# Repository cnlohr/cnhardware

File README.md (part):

# hardware

My random junk repo for random things.

If you're looking for 

**NOTE** FOR PULL REQUESTS: I DO NOT ACCEPT MASS ADDS.  If you have 5-6 really awesome parts, I'll accept a pull request, but if you have say 10+ parts, I will not.  Select only the neatest.  Also, make sure JLCPCB offers the parts, if they're intended for board mounting!

## Shortcuts

* [Discussion of ferrite cores and what their recommended power is](https://www.mag-inc.com/Media/Magnetics/File-Library/Product%20Literature/Ferrite%20Literature/Ferrite-Transformer-Design-2021.pdf)
* [Another doc like the above, but with different info](https://www.mag-inc.com/getattachment/Products/Ferrite-Cores/MagneticsFerritePowerDesign2013.pdf?)
* [Discussion of building ferrite cores](https://www.st.com/resource/en/newsletter/Wurth_Design_Considerations_Munich.pdf)
* [Breakdown voltages of enameld copper wire](https://www.edaboard.com/threads/breakdown-voltage-of-enamelled-copper-wire.407275/)
* [Enameld wire datasheet](https://www.elektrisola.com/en-us/Products/Enamelled-Wire/Technical-Data)

## Small Combo Fets

|Datasheet|LCSC|Footprint|Description|Cost 150|
|--|--|--|--|--|
|[PB544JU](https://datasheet.lcsc.com/lcsc/2005181005_NIKO-Semicon-PB544JU_C532969.pdf)|[C532969](https://www.lcsc.com/product-detail/MOSFETs_NIKO-Semicon-PB544JU_C532969.html)|DFN-6-EP(3x2)|Dual N 20v, 8m, 1.2v, 1584pF|0.1376|
|[SE4625](https://datasheet.lcsc.com/lcsc/2008291435_SINO-IC-SE4625_C730094.pdf)|[C730094](https://www.lcsc.com/product-detail/MOSFETs_SINO-IC-SE4625_C730094.html)|DFN-6L-EP(2x2)|P and N, 12v, 28/57m, 1.2v, 469pF|0.0508|
|[SED5852](https://datasheet.lcsc.com/lcsc/2208251800_SINO-IC-SED5852_C238715.pdf)|[C238715](https://www.lcsc.com/product-detail/MOSFETs_SINO-IC-SED5852_C238715.html)|DFN-6-EP(2x2)|P+Schottky, 20v, 90m, 1.2v, 540pF|0.0250|
|[WPM2006](https://datasheet.lcsc.com/lcsc/1808311525_WILLSEMI-Will-Semicon-WPM2006-6-TR_C167136.pdf)|[C167136](https://www.lcsc.com/product-detail/MOSFETs_WILLSEMI-Will-Semicon-WPM2006-6-TR_C167136.html)|DFN-6L-EP(2x2)|P+Schottky, 20v, 90m, 1.2v, 480pF|0.0579|
|[YJQ2301A](https://datasheet.lcsc.com/lcsc/2206101730_Yangzhou-Yangjie-Elec-Tech-YJQ2301A_C2942370.pdf)|[C2942370](https://www.lcsc.com/product-detail/MOSFETs_Yangzhou-Yangjie-Elec-Tech-YJQ2301A_C2942370.html)|DFN-6-EP(2x2)|Dual P 20v, 60m, 1.2v, 438pF|0.0872**|
|[HSCB20D03](https://datasheet.lcsc.com/lcsc/2105241828_HUASHUO-HSCB20D03_C2828494.pdf)|[C2828494](https://www.lcsc.com/product-detail/MOSFETs_HUASHUO-HSCB20D03_C2828494.html)|DFN-6-EP(2x2)|Dual P 20v, 90m, 1.5v, 331pF|0.0927|
|[HSCB2903](https://datasheet.lcsc.com/lcsc/2110221630_HUASHUO-HSCB2903_C2903561.pdf)|[C2903561](https://www.lcsc.com/product-detail/MOSFETs_HUASHUO-HSCB2903_C2903561.html)|DFN-6L-EP(2x2)|P and N, 20v, 40m, 100m, 1.5v, 310pF|0.1273||
|[NCE30D0808J](https://datasheet.lcsc.com/lcsc/2103121415_Wuxi-NCE-Power-Semiconductor-NCE30D0808J_C2686534.pdf)|[C2686534](https://www.lcsc.com/product-detail/MOSFETs_Wuxi-NCE-Power-Semiconductor-NCE30D0808J_C2686534.html)|DFN-6-EP(2x2)|Dual N, 30v, 35m, 2.5v, 558pF|0.1729|
|[SIA517DJ-T1-GE3](https://datasheet.lcsc.com/lcsc/2108150330_JSMSEMI-SIA517DJ-T1-GE3_C2874705.pdf)|[C2874705](https://www.lcsc.com/product-detail/MOSFETs_JSMSEMI-SIA517DJ-T1-GE3_C2874705.html)|WDFN-6-EP(2x2)|P and N, 12v, 30/70m, 590pF|0.1764|
|[DMP1046UFDB-7](https://datasheet.lcsc.com/lcsc/1912111437_Diodes-Incorporated-DMP1046UFDB-7_C461048.pdf)|[C461048](https://www.lcsc.com/product-detail/MOSFETs_Diodes-Incorporated-DMP1046UFDB-7_C461048.html)|U-DFN2020-6D|Dual N, 12v, 60m, 1.3v, 915pF|0.20|

## Interesting Fets

|Datasheet|LCSC|Footprint|Description|Cost 150|
|--|--|--|--|--|
|[WNM2096-3/TR](https://datasheet.lcsc.com/lcsc/2201121500_WILLSEMI-Will-Semicon-WNM2096-3-TR_C2931326.pdf)**|[C2931326](https://www.lcsc.com/product-detail/MOSFETs_WILLSEMI-Will-Semicon-WNM2096-3-TR_C2931326.html)|DFN-3(1x0.6)|N, 20v, 400m, 1.7v, 20pF (On Order)|0.0626|
|[TPDMN26D0UFB4](https://datasheet.lcsc.com/lcsc/2108132030_TECH-PUBLIC-TPDMN26D0UFB4_C970037.pdf)|[C970037](https://www.lcsc.com/product-detail/MOSFETs_TECH-PUBLIC-TPDMN26D0UFB4_C970037.html)|DFN-3(1x0.6)|N, 20v, 500m, 1.2v, 120pF (Cheap, Basic Sevice, Tiny, Not great but good for signals)|.0242|
|[DMN3110LCP3-7](https://datasheet.lcsc.com/lcsc/1912111437_Diodes-Incorporated-DMN3110LCP3-7_C443826.pdf)|[C443826](https://www.lcsc.com/product-detail/MOSFETs_Diodes-Incorporated-DMN3110LCP3-7_C443826.html)|X2-DSN1006-3|N, 30v, 80m, 1.3v, 140pF Wicked Awesome Case|0.1775|
|[TPM2008EP3](https://datasheet.lcsc.com/lcsc/2108132030_TECH-PUBLIC-TPM2008EP3_C2682293.pdf)|[C2682293](https://www.lcsc.com/product-detail/MOSFETs_TECH-PUBLIC-TPM2008EP3_C2682293.html)|DFN1006-3L(1x0.6)|N, 20v, 130m, 1.2v, 120pF|0.0278|
|[PNM3FD20V1E](https://datasheet.lcsc.com/lcsc/2108150430_Shanghai-Prisemi-Elec-PNM3FD20V1E_C2875806.pdf)|[C2875806](https://www.lcsc.com/product-detail/MOSFETs_Shanghai-Prisemi-Elec-PNM3FD20V1E_C2875806.html)|DFN-3L(1x0.6)|N, 20v, 200m, 1.1v, 48pF|0.0256|
|[DMN2990UFA-7B](https://datasheet.lcsc.com/lcsc/1804250226_Diodes-Incorporated-DMN2990UFA-7B_C151598.pdf)|[C151598](https://www.lcsc.com/product-detail/MOSFETs_Diodes-Incorporated-DMN2990UFA-7B_C151598.html)|XFDFN-3(0.6x0.8)|N, 20v, 900m, 1.3v, 30pF|0.0544|
|[HSCB2307](https://datasheet.lcsc.com/lcsc/2010160905_HUASHUO-HSCB2307_C845602.pdf)|[C845602](https://www.lcsc.com/product-detail/MOSFETs_HUASHUO-HSCB2307_C845602.html)|DFN-6L(2x2)|P, 20v, 15m, 1v, 2100pF|0.0789|
|[G66](https://datasheet.lcsc.com/lcsc/1809251724_GOFORD-G66_C239037.pdf)|[C239037](https://www.lcsc.com/product-detail/MOSFETs_GOFORD-G66_C239037.html)|DFN-6L(2x2)|P, 16v, 45m, 1.25v, 740pF|0.0499|
|[DMP1009UFDF](https://datasheet.lcsc.com/lcsc/2003091237_Diodes-Incorporated-DMP1009UFDF-7_C493499.pdf)|[C493499](https://www.lcsc.com/product-detail/MOSFETs_Diodes-Incorporated-DMP1009UFDF-7_C493499.html)|U-DFN2020-6|P, 12v, 11m, 1.1v, 1860pF|0.4530|
|[PJM01N20KDC](https://datasheet.lcsc.com/lcsc/2203092030_PJSEMI-PJM01N20KDC_C2981470.pdf)|[C2981470](https://www.lcsc.com/product-detail/MOSFETs_PJSEMI-PJM01N20KDC_C2981470.html)|DFN-3L(1x0.6)|N, 20v, 180m, 1.3v, 56pF|0.0259|
|[AP4580](https://datasheet.lcsc.com/lcsc/2108150030_ALLPOWER-ShenZhen-Quan-Li-Semiconductor-AP4580_C2849569.pdf)|[C2849569](https://www.lcsc.com/product-detail/MOSFETs_ALLPOWER-ShenZhen-Quan-Li-Semiconductor-AP4580_C2849569.html)|SOT-23-8L|2N and 2P Full Bridge|0.0635|
|[DMC3730UFL3-7](https://datasheet.lcsc.com/lcsc/1912111437_Diodes-Incorporated-DMC3730UFL3-7_C460973.pdf)|[C460973](https://www.lcsc.com/product-detail/MOSFETs_Diodes-Incorporated-DMC3730UFL3-7_C460973.html)|X2-DFN1310-6|Complementary P- and N- 1A, 30V TTL level FETs|0.0539|

## Special FETs

|Datasheet|LCSC|Footprint|Description|Cost 150|
|--|--|--|--|--|
|[DMZ6005E](https://datasheet.lcsc.com/lcsc/2206061716_ARK-micro-DMZ6005E_C3031422.pdf)|[C3031422](https://www.lcsc.com/product-detail/MOSFETs_ARK-micro-DMZ6005E_C3031422.html)|SOT-23|Depletion Mode N-Fet (Normally on)|0.0626|

## Interesting BJTs

|Datasheet|LCSC|Footprint|Description|Cost 150|
|--|--|--|--|--|
|[2SC4226](https://datasheet.lcsc.com/lcsc/2009141834_Slkor-SLKORMICRO-Elec--2SC4226-R25_C781319.pdf)|[C781319](https://www.lcsc.com/product-detail/Bipolar-Transistors-BJT_Slkor-SLKORMICRO-Elec-2SC4226-R25_C781319.html)|SOT-323-3|4.5GHz, 20V 100mA, 100 Hfe, +16dB@433MHz|0.0269|
|[2SC4228](https://datasheet.lcsc.com/lcsc/2009141834_Slkor-SLKORMICRO-Elec--2SC4228-R45_C781327.pdf)|[C781327](https://www.lcsc.com/product-detail/Bipolar-Transistors-BJT_Slkor-SLKORMICRO-Elec-2SC4228-R45_C781327.html)|SOT-323-3|8GHz, 20V 35mA, 150 Hfe, +19dB@433MHz|0.0464|
|[2SC4901](https://datasheet.lcsc.com/lcsc/2009141834_Slkor-SLKORMICRO-Elec--2SC4901_C781326.pdf)|[C781326](https://www.lcsc.com/product-detail/Bipolar-Transistors-BJT_Slkor-SLKORMICRO-Elec-2SC4901_C781326.html)|SOT-323-3|9GHz, 11V, 150 Hfe, +21dB@433MHz|0.0508|

## Diodes

|Datasheet|LCSC|Footprint|Description|Cost 150|
|--|--|--|--|--|
|[TPLMBR01S30ST5G](https://datasheet.lcsc.com/lcsc/2108150230_TECH-PUBLIC-TPLMBR01S30ST5G_C2858725.pdf)|[C2858725](https://www.lcsc.com/product-detail/Schottky-Barrier-Diodes-SBD_TECH-PUBLIC-TPLMBR01S30ST5G_C2858725.html)|DFN0603 (0.6x0.3)|Schottky, 30v, 0.35v, 100mA|0.0231|
|[WSB5539N-2/TR](https://datasheet.lcsc.com/lcsc/1808311538_WILLSEMI-Will-Semicon-WSB5539N-2-TR_C239808.pdf)|[C239808](https://www.lcsc.com/product-detail/Schottky-Barrier-Diodes-SBD_WILLSEMI-Will-Semicon-WSB5539N-2-TR_C239808.html)|DFN1006-2L|Schottky, 40v, 0.53v, 500mA (250mV@10mA),(350mV@100mA) (20pF)|0.0569|
|[PMEG3010EJ,115](https://datasheet.lcsc.com/lcsc/1810231722_Nexperia-PMEG3010EJ-115_C255586.pdf)***|[C255586](https://www.lcsc.com/product-detail/Schottky-Barrier-Diodes-SBD_Nexperia-PMEG3010EJ-115_C255586.html)|SOD-323F|Schottky, 30v, 0.25v, 1A (210mV@10mA),(290mV@100mA) (30pF)|0.1470|
|[1N4448HLP-7](https://datasheet.lcsc.com/lcsc/1912111437_Diodes-Incorporated-1N4448HLP-7_C154874.pdf)|[C154874](https://www.lcsc.com/product-detail/Switching-Diode_Diodes-Incorporated-1N4448HLP-7_C154874.html)|DFN-2(0.6x1)|Switching, 80v, 0.8v, 300mA|0.0232|
|[PMEG3010AESBYL](https://datasheet.lcsc.com/lcsc/2004031109_Nexperia-PMEG3010AESBYL_C503409.pdf)|[C503409](https://www.lcsc.com/product-detail/Schottky-Barrier-Diodes-SBD_Nexperia-PMEG3010AESBYL_C503409.html)|DFN1006-2L|Schottky, 1A,(200mV@10mA),(280mV@100mA) (40pF) Wicked Awesome Case|0.0936|

## TVS

|Datasheet|LCSC|Footprint|Description|Cost 150|
|--|--|--|--|--|
|[USBLC6-2P6](https://datasheet.lcsc.com/lcsc/2108132230_TECH-PUBLIC-USBLC6-2P6_C2827693.pdf)|[C2827693](https://www.lcsc.com/product-detail/ESD-Protection-Devices_TECH-PUBLIC-USBLC6-2P6_C2827693.html)|SOT-666-6|USB TVS only 2 TVS channels, 5V Operating Voltage|0.0666|

## Various LiPo / LiIon Chips

|Datasheet|LCSC|Footprint|Description|Cost 150|
|--|--|--|--|--|
|[RY2200](https://datasheet.lcsc.com/lcsc/2108251630_RYCHIP-Semiconductor-Inc--RY2200_C2888102.pdf)|[C2888102](https://www.lcsc.com/product-detail/Battery-Management-ICs_RYCHIP-Semiconductor-Inc-RY2200_C2888102.html)|SOT-23|Battery Protection|0.0431|
|[LGS4056H](https://datasheet.lcsc.com/lcsc/2210111600_Legend-Si-LGS4056H_C5124109.pdf)|[C5124109](https://www.lcsc.com/product-detail/Battery-Management-ICs_Legend-Si-LGS4056H_C5124109.html)|DFN-8(2x2)|Battery Charger, 1A|0.0891|
|[XB6042J2SV-L](https://datasheet.lcsc.com/lcsc/2104081605_XySemi-XB6042J2SV-L_C2759994.pdf)|[C2759994](https://www.lcsc.com/product-detail/Battery-Management-ICs_XySemi-XB6042J2SV-L_C2759994.html)|DFN1X1x0.37-4|Battery Protection, 44mO|0.1160|
|[LP4069TQVF](https://datasheet.lcsc.com/lcsc/2108271830_LOWPOWER-LP4069TQVF_C2890382.pdf)|[C2890382](https://www.lcsc.com/product-detail/Battery-Management-ICs_LOWPOWER-LP4069TQVF_C2890382.html)|DFN-8-EP(2x2)|Battery Charger 800mA (English Datasheet)|0.2010|
|[HP4555D8-42](https://datasheet.lcsc.com/lcsc/2006301234_HYPWR-HP4555D8-42_C648897.pdf)|[C648899](https://www.lcsc.com/product-detail/Battery-Management-ICs_HYPWR-HP4555D8-44_C648899.html)|DFN-8-EP(2x2)|Battery Charger 500mA (English Datasheet)|0.1171|
|[LP28013QVF](https://datasheet.lcsc.com/lcsc/2004281204_LOWPOWER-LP28013QVF-44_C517140.pdf)|[C517140](https://www.lcsc.com/product-detail/Battery-Management-ICs_LOWPOWER-LP28013QVF-44_C517140.html)|TDFN-10-EP(3x3)|Battery Charger (English, Interesting Blocking config) WARNING: NOT 4.2V|0.1975|
|[LP5301QVF](https://datasheet.lcsc.com/lcsc/2004281203_LOWPOWER-LP5301QVF_C517041.pdf)|[C517041](https://www.lcsc.com/product-detail/Battery-Management-ICs_LOWPOWER-LP5301QVF_C517041.html)|DFN-8-EP(2x2)|Battery Charger (English, No Blocking Diode, for backflow Structure)|0.1983|
|[WS4518D-6/TR](https://datasheet.lcsc.com/lcsc/2011111834_WILLSEMI-Will-Semicon-WS4518D-6-TR_C910991.pdf)|[C910991](https://www.lcsc.com/product-detail/Battery-Management-ICs_WILLSEMI-Will-Semicon-WS4518D-6-TR_C910991.html)|DFN-8-EP(2x2)|Battery Charger (English, Willsemi, Cheap)|0.1121|
|[XB6042Q2SV-L](https://datasheet.lcsc.com/lcsc/2104081605_XySemi-XB6042Q2SV-L_C2759995.pdf)|[C2759995](https://www.lcsc.com/product-detail/Battery-Management-ICs_XySemi-XB6042Q2SV-L_C2759995.html)|DFN-4-EP(1x1)|Protection (4.2/4.25v) 44mO|0.1160|
|[SGM41562BXG/TR](https://datasheet.lcsc.com/lcsc/2302061809_SGMICRO-SGM41562BXG-TR_C5153801.pdf)|[C5153801](https://www.lcsc.com/product-detail/Battery-Management-ICs_SGMICRO-SGM41562BXG-TR_C5153801.html)|WLCSP-9-B(1.52x1.52)|Charger + Power Path for LiPo/LiIon + I2C + Power Down Options|0.4137|
|[AW32001ECSR](https://www.lcsc.com/product-detail/Battery-Management-ICs_AWINIC-Shanghai-Awinic-Tech-AW32001ECSR_C5125890.html)|[C5125890](https://www.lcsc.com/product-detail/Battery-Management-ICs_AWINIC-Shanghai-Awinic-Tech-AW32001ECSR_C5125890.html)|WLCSP-9-B(1.68x1.68)|Charger + Power Path for LiPo/LiIon + I2C + Power Down Options *Has good power off* I intend to use this.|0.2642-0.3675|

## Flash Chips

|Datasheet|LCSC|Footprint|Description|Cost 150|
|--|--|--|--|--|
|[GD25LE64ELIGR](https://datasheet.lcsc.com/lcsc/2208221030_GigaDevice-Semicon-Beijing-GD25LE64ELIGR_C2904424.pdf)|[C2904424](https://www.lcsc.com/product-detail/NOR-FLASH_GigaDevice-Semicon-Beijing-GD25LE64ELIGR_C2904424.html)|WLCSP-8 (1.35x2.75)|NOR Flash, 64Mbit, 1.65-2v, 133MHz, 4x|0.6938|
|[ZD25WQ32CEIGR](https://datasheet.lcsc.com/lcsc/2211091800_Zetta-ZD25WQ32CEIGR_C5258281.pdf)|[C5258281](https://www.lcsc.com/product-detail/NOR-FLASH_Zetta-ZD25WQ32CEIGR_C5258281.html)|USON8-LINE(2x3)|NOR Flash, 32Mbit, 1.65-3.6v, 104MHz, 4x|0.1846|
|[P25Q32H-UXH-IR](https://datasheet.lcsc.com/lcsc/1912111437_PUYA--P25Q32H-UXH-IR_C414068.pdf)|[C414068](https://www.lcsc.com/product-detail/span-style-background-color-ff0-NOR-span-span-style-background-color-ff0-FLASH-span_PUYA-P25Q32H-UXH-IR_C414068.html)|USON8-EP(2x3)|NOR Flash, 32Mbit, 2.3-3.6v, 120MHz|0.3162|
|[ZD25WQ16BUIGR](https://datasheet.lcsc.com/lcsc/2203161812_Zetta-ZD25WQ16BUIGR_C2983691.pdf)|[C2983691](https://www.lcsc.com/product-detail/NOR-FLASH_Zetta-ZD25WQ16BUIGR_C2983691.html)|USON-8(2x3)|NOR Flash, 16Mbit, 1.65-3.6v, 104MHz|0.1782|
|[ZD25WD40BUIGR](https://datasheet.lcsc.com/lcsc/2204011630_Zetta-ZD25WD40BUIGR_C2759917.pdf)|[C2759917](https://www.lcsc.com/product-detail/span-style-background-color-ff0-NOR-span-span-style-background-color-ff0-FLASH-span_Zetta-ZD25WD40BUIGR_C2759917.html)|USON-8(2x3)|NOR Flash, 4Mbit, 1.65-2.0v, 104MHz (DIO ONLY)|0.0546|
|[ZD25WD20BUIGR](https://datasheet.lcsc.com/lcsc/2106062209_Zetta-ZD25WD20BUIGR_C2759918.pdf)|[C2759918](https://www.lcsc.com/product-detail/span-style-background-color-ff0-NOR-span-span-style-background-color-ff0-FLASH-span_Zetta-ZD25WD20BUIGR_C2759918.html)|USON-8(2x3)|NOR Flash, 2Mbit, 1.65-3.6v, 104MHz (DIO ONLY)|0.0675|
|[ZD25Q80BNIGR](https://datasheet.lcsc.com/lcsc/2206131630_Zetta-ZD25Q80BNIGR_C3035284.pdf)|[C3035284](https://www.lcsc.com/product-detail/NOR-FLASH_Zetta-ZD25Q80BNIGR_C3035284.html)|USON-8(1.5x1.5)|NOR Flash, 8Mbit, 2.3-3.6v, 104MHz (QIO ok)|0.18|
|[GD25Q128ESIGR](https://datasheet.lcsc.com/lcsc/2204011730_GigaDevice-Semicon-Beijing-GD25Q128EWIG_C2986327.pdf)|[C2928891](https://www.lcsc.com/product-detail/span-style-background-color-ff0-NOR-span-span-style-background-color-ff0-FLASH-span_GigaDevice-Semicon-Beijing-GD25Q128ESIGR_C2928891.html)|SOP-8-208mil|128 Mbit (16MByte) Flash Chip|0.7588|
|[W25Q64JVXGIQ](https://datasheet.lcsc.com/lcsc/2201121830_Winbond-Elec-W25Q64JVXGIQ_C2940195.pdf)|[C2940195](https://www.lcsc.com/product-detail/NOR-FLASH_Winbond-Elec-W25Q64JVXGIQ_C2940195.html)|USON-4x4|3.0-3.6V, 64Mbit, Dual, Quad SPI|.4964|

## RAM

|Datasheet|LCSC|Footprint|Description|Cost 150|
|--|--|--|--|--|
|[VTI7064MSME](https://datasheet.lcsc.com/lcsc/1811151432_Vilsion-Tech-VTI7064MSME_C139966.pdf)|[C139966](https://www.lcsc.com/product-detail/SRAM_Vilsion-Tech-VTI7064MSME_C139966.html)|SOP-8 (4.8mm pad centers)|64-MBit PSRAM 2.7-3.3V|3.7339|

## PCI Express

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
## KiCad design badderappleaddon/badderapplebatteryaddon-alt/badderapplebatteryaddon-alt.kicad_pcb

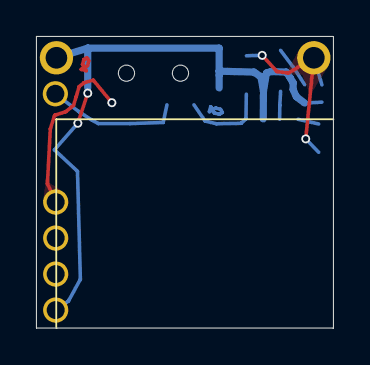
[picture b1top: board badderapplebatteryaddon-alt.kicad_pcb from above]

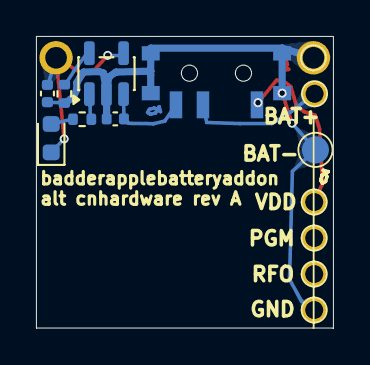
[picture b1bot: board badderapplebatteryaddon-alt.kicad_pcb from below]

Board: 2 copper layers, 16.5 x 16.2 mm, 15 parts (14 on the bottom side), 8 nets.

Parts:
C6, C7: 4.7u; C_0402_1005Metric
D3: LED; LED_0603_1608Metric
J3: PGM; TestPoint_Pad_D1.0mm
J4: VDD; TestPoint_Pad_D1.0mm
J5, J11: GND; TestPoint_Pad_D1.0mm
J6: RFO; TestPoint_Pad_D1.0mm
J7: BAT+; TestPoint_Pad_D1.0mm
J10: VBUS
R14: 1k; R_0402_1005Metric
R15: 10k; R_0402_1005Metric
SW1: PWR; SW_SPDT_PCM12
TP13: BAT-; TestPoint_Pad_D1.5mm
U3: SOT-23-5

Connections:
GND: C6.2, C7.2, J5.1 (1_1), J11.1 (1_1), R15.2, SW1.4, SW1.5, SW1.6, SW1.7, TP13.1 (1_1), U3.2 (GND)
unnamed: D3.2 (A), R14.1
unnamed: C7.1, SW1.3, U3.3 (BAT)
unnamed: R15.1, U3.5 (PROG)
unnamed: R14.2, U3.1 (~CHRG)
VBAT: J7.1 (1_1), SW1.2
VBUS: C6.1, D3.1 (K), J10.1 (1_1), U3.4 (VCC)
VDD: J4.1 (1_1), SW1.1

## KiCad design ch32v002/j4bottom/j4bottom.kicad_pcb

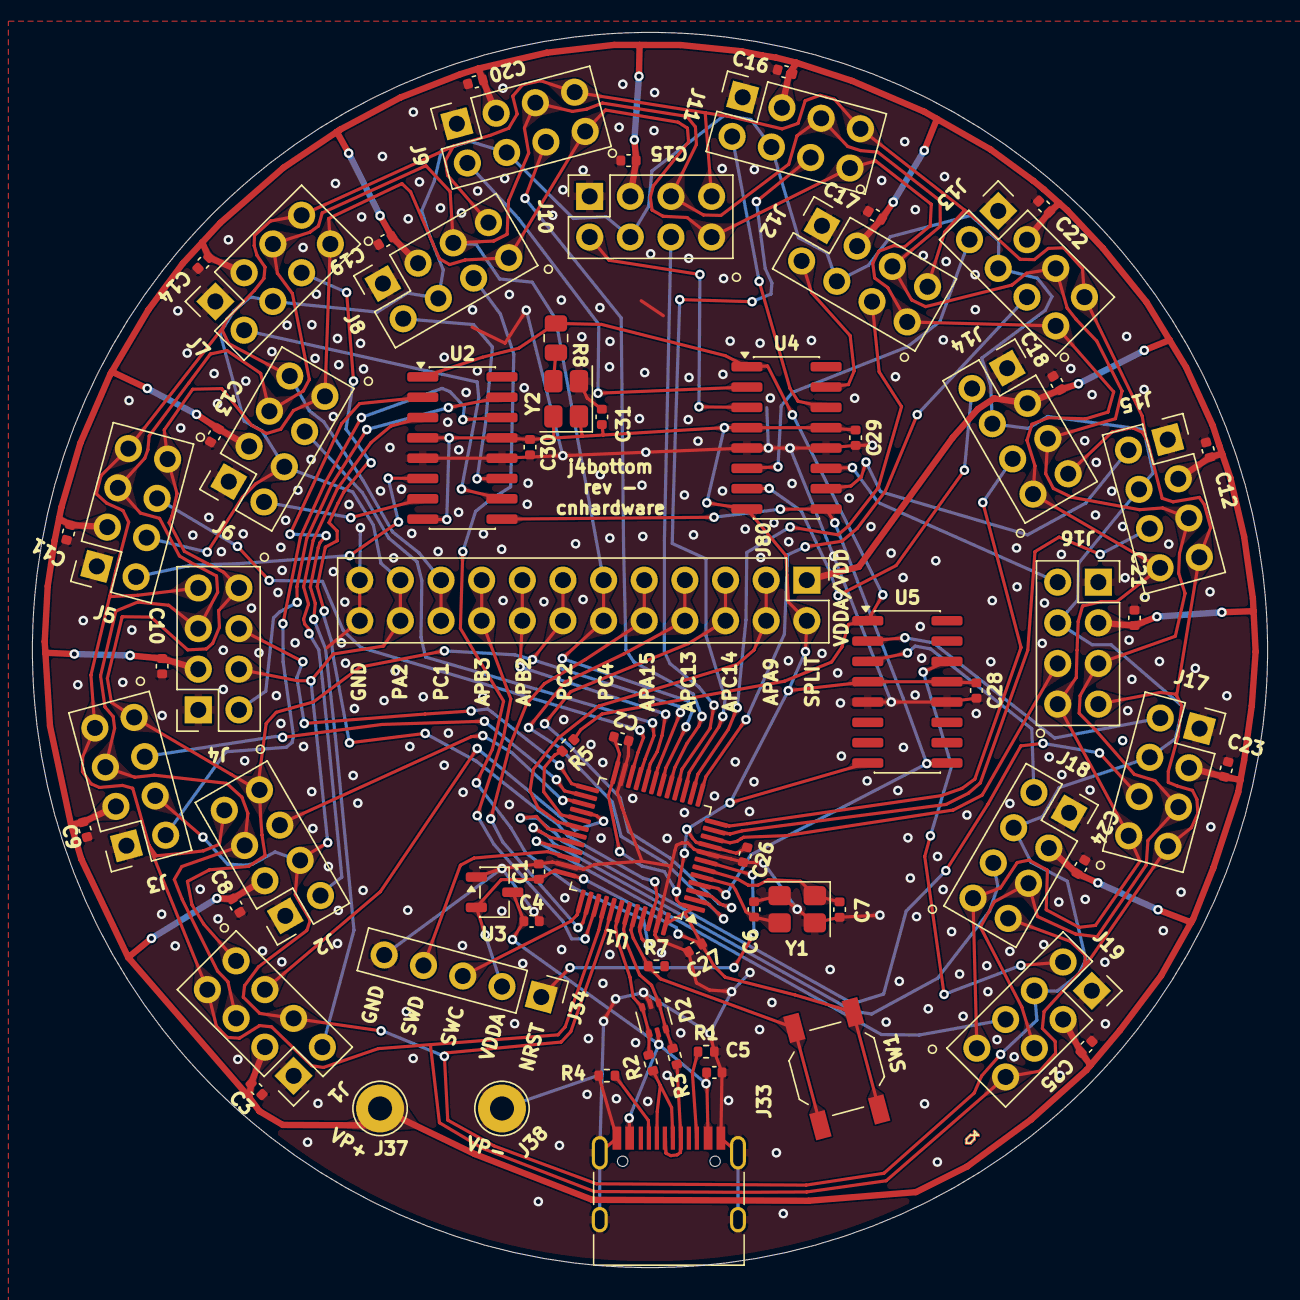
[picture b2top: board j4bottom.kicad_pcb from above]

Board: 2 copper layers, 77.2 x 77.2 mm, 71 parts (0 on the bottom side), 68 nets.

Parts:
C1, C3, C5, C8, C9, C10, C11, C12, C13, C14, C15, C16, C17, C18, C19, C20, C21, C22, C23, C24, C25: 4.7u; C_0402_1005Metric
C2, C4, C26, C27, C28, C29, C30, C31: 0.1u; C_0402_1005Metric
C6, C7: 10p; C_0402_1005Metric
D2: USBLC6-2P6-TVS; SOT-666
J1, J2, J3, J4, J5, J6, J7, J8, J9, J10, J11, J12, J13, J14, J15, J16, J17, J18, J19: PinSocket_2x04_P2.54mm_Vertical
J33: USB_C_Receptacle_USB2.0; USB_C_2.5
J34: PGM; PinHeader_1x05_P2.54mm_Vertical
J37: VP+; TestPoint_Loop_D2.54mm_Drill1.5mm_Beaded
J38: VP-; TestPoint_Loop_D2.54mm_Drill1.5mm_Beaded
J80: Conn_02x12_Odd_Even; PinHeader_2x12_P2.54mm_Vertical
R1, R4, R7: 5.1k; R_0402_1005Metric
R2, R3, R5: 22; R_0402_1005Metric
R8: 0; R_0805_2012Metric
SW1: Download; SW_SPST_TL3342
U1: CH32V30xCxTx; LQFP-48_7x7mm_P0.5mm
U2, U4, U5: SOIC-16_3.9x9.9mm_P1.27mm
U3: XC6206PxxxMR; SOT-23-3
Y1: 8MHz12pF; Crystal_SMD_3225-4Pin_3.2x2.5mm
Y2: 27.63636MHz; Crystal_SMD_SeikoEpson_TSX3225-4Pin_3.2x2.5mm

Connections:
+5V: C4.1, C5.1, D2.5 (VB), J33.A4 (VBUS), J33.A9 (VBUS), J33.B4 (VBUS), J33.B9 (VBUS), U3.3 (VI)
APA9: J80.3, J80.4, U1.30 (PA9)
APA15: J80.9, J80.10, U1.38 (PA15)
APB2: J80.15, J80.16, U1.20 (PB2)
APB3: J80.17, J80.18, U1.39 (PB3)
APC13: J80.7, J80.8, U1.2 (PC13)
APC14: J80.5, J80.6, U1.3 (PC14)
BOOT0: R7.1, SW1.2 (B), U1.44 (BOOT0)
CLK0: J1.2, U2.2 (CLKA1)
CLK1: J2.2, U2.3 (CLKA2)
CLK2: J3.2, U2.14 (CLKA3)
CLK3: J4.2, U2.15 (CLKA4)
CLK4: J5.2, U2.6 (CLKB1)
CLK5: J6.2, U2.7 (CLKB2)
CLK6: J7.2, U2.10 (CLKB3)
CLK7: J8.2, U2.11 (CLKB4)
CLK8: J9.2, U4.2 (CLKA1)
CLK9: J10.2, U4.3 (CLKA2)
CLK10: J11.2, U4.14 (CLKA3)
CLK11: J12.2, U4.15 (CLKA4)
CLK12: J13.2, U4.6 (CLKB1)
CLK13: J14.2, U4.7 (CLKB2)
CLK14: J15.2, U4.10 (CLKB3)
CLK15: J16.2, U4.11 (CLKB4)
CLK16: J17.2, U5.2 (CLKA1)
CLK17: J18.2, U5.3 (CLKA2)
CLK18: J19.2, U5.14 (CLKA3)
D+: D2.1 (IO1), D2.6 (IO1), R3.2, U1.43 (PB7)
D-: D2.3 (IO2), D2.4 (IO2), R2.2, U1.42 (PB6)
GND: C1.2, C2.2, C3.2, C4.2, C5.2, C6.1, C7.1, C8.2, C9.2, C10.2, C11.2, C12.2, C13.2, C14.2, C15.2, C16.2, C17.2, C18.2, C19.2, C20.2, C21.2, C22.2, C23.2, C24.2, C25.2, C26.2, C27.2, C28.2, C29.2, C30.2, C31.2, D2.2 (GND), J1.1, J2.1, J3.1, J4.1, J5.1, J6.1, J7.1, J8.1, J9.1, J10.1, J11.1, J12.1, J13.1, J14.1, J15.1, J16.1, J17.1, J18.1, J19.1, J33.A1 (GND), J33.A12 (GND), J33.B1 (GND), J33.B12 (GND), J33.S1 (SHIELD), J34.5, J38.1 (Pin_1_1), J80.23, J80.24, R1.2, R4.2, U1.8 (VSSA), U1.23 (VSS), U1.35 (VSS), U1.47 (VSS), U2.5 (GND), U2.12 (GND), U3.1 (GND), U4.5 (GND), U4.12 (GND), U5.5 (GND), U5.12 (GND), Y1.2, Y1.4, Y2.2 (GND)
MCO: R5.1, R8.2, U2.1 (REF), U4.1 (REF), U5.1 (REF)
NRST: J34.1, U1.7 (~RST)
unnamed: J33.A5 (CC1), R4.1
unnamed: J33.B5 (CC2), R1.1
unnamed: J33.A6 (D+), J33.B6 (D+), R3.1
unnamed: J33.A7 (D-), J33.B7 (D-), R2.1
unnamed: R5.2, U1.29 (PA8)
unnamed: R8.1, Y2.3 (OUT)
OSCI: C6.2, U1.5 (OSC_IN), Y1.3
OSCO: C7.2, U1.6 (OSC_OUT), Y1.1
PA2: J1.4, J2.4, J3.4, J4.4, J5.4, J6.4, J7.4, J8.4, J9.4, J10.4, J11.4, J12.4, J13.4, J14.4, J15.4, J16.4, J17.4, J18.4, J19.4, J80.21, J80.22, U1.41 (PB5)
PC1: J1.7, J2.7, J3.7, J4.7, J5.7, J6.7, J7.7, J8.7, J9.7, J10.7, J11.7, J12.7, J13.7, J14.7, J15.7, J16.7, J17.7, J18.7, J19.7, J80.19, J80.20, U1.40 (PB4)
PC2: J1.8, J2.8, J3.8, J4.8, J5.8, J6.8, J7.8, J8.8, J9.8, J10.8, J11.8, J12.8, J13.8, J14.8, J15.8, J16.8, J17.8, J18.8, J19.8, J80.13, J80.14, U1.19 (PB1)
PC4: J1.5, J2.5, J3.5, J4.5, J5.5, J6.5, J7.5, J8.5, J9.5, J10.5, J11.5, J12.5, J13.5, J14.5, J15.5, J16.5, J17.5, J18.5, J19.5, J80.11, J80.12, U1.18 (PB0)
SCTL: U1.4 (PC15), U2.9 (S1), U4.9 (S1), U5.9 (S1)
SWC: J34.3, U1.37 (SWCLK)
SWD: J34.4, U1.34 (SWDIO)
SWIO0: J1.6, U1.28 (PB15)
SWIO1: J2.6, U1.27 (PB14)
SWIO2: J3.6, U1.26 (PB13)
SWIO3: J4.6, U1.25 (PB12)
SWIO4: J5.6, U1.22 (PB11)
SWIO5: J6.6, U1.21 (PB10)
SWIO6: J7.6, U1.46 (PB9)
SWIO7: J8.6, U1.45 (PB8)
SWIO8: J9.6, U1.17 (PA7)
SWIO9: J10.6, U1.16 (PA6)
SWIO10: J11.6, U1.15 (PA5)
SWIO11: J12.6, U1.14 (PA4)
SWIO12: J13.6, U1.13 (PA3)
SWIO13: J14.6, U1.12 (PA2)
SWIO14: J15.6, U1.11 (PA1)
SWIO15: J16.6, U1.10 (PA0)
SWIO16: J17.6, U1.31 (PA10)
SWIO17: J18.6, U1.32 (PA11)
SWIO18: J19.6, U1.33 (PA12)
VDD: C3.1, C8.1, C9.1, C10.1, C11.1, C12.1, C13.1, C14.1, C15.1, C16.1, C17.1, C18.1, C19.1, C20.1, C21.1, C22.1, C23.1, C24.1, C25.1, J1.3, J2.3, J3.3, J4.3, J5.3, J6.3, J7.3, J8.3, J9.3, J10.3, J11.3, J12.3, J13.3, J14.3, J15.3, J16.3, J17.3, J18.3, J19.3, J37.1 (Pin_1_1), J80.1
VDDA: C1.1, C2.1, C26.1, C27.1, C28.1, C29.1, C30.1, C31.1, J34.2, J80.2, SW1.1 (A), U1.1 (VBAT), U1.9 (VDDA), U1.24 (VDD), U1.36 (VDD), U1.48 (VDD), U2.4 (VDD), U2.8 (S2), U2.13 (VDD), U3.2 (VO), U4.4 (VDD), U4.8 (S2), U4.13 (VDD), U5.4 (VDD), U5.8 (S2), U5.13 (VDD), Y2.1 (Tri-State), Y2.4 (VDD)

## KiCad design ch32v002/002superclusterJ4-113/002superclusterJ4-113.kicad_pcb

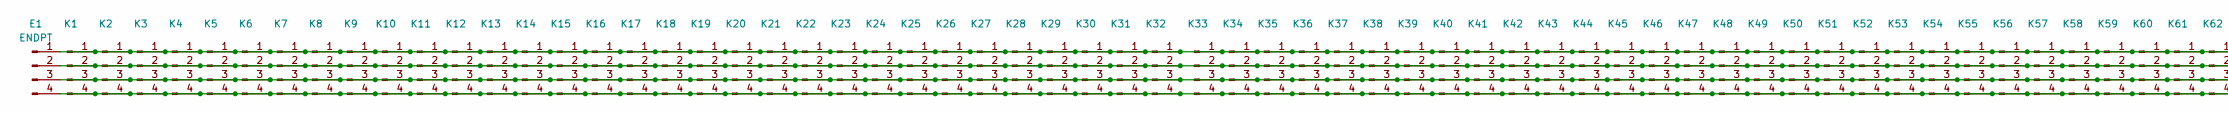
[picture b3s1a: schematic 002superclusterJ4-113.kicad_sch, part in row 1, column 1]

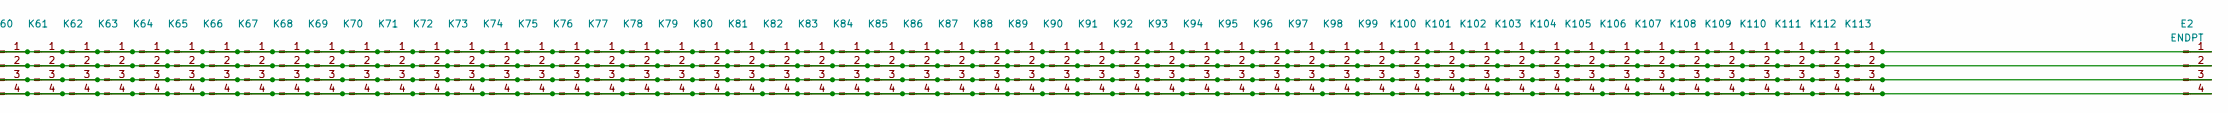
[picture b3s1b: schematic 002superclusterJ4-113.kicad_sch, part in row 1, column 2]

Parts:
E1, E2: ENDPT; EDGE_02x02_2.54mm
K1, K2, K3, K4, K5, K6, K7, K8, K9, K10, K11, K12, K13, K14, K15, K16, K17, K18, K19, K20, K21, K22, K23, K24, K25, K26, K27, K28, K29, K30, K31, K32, K33, K34, K35, K36, K37, K38, K39, K40, K41, K42, K43, K44, K45, K46, K47, K48, K49, K50, K51, K52, K53, K54, K55, K56, K57, K58, K59, K60, K61, K62, K63, K64, K65, K66, K67, K68, K69, K70, K71, K72, K73, K74, K75, K76, K77, K78, K79, K80, K81, K82, K83, K84, K85, K86, K87, K88, K89, K90, K91, K92, K93, K94, K95, K96, K97, K98, K99, K100, K101, K102, K103, K104, K105, K106, K107, K108, K109, K110, K111, K112, K113: PinHeader_1x04_P1.27mm_Vertical

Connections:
unnamed: E1.1, E2.1, K1.1, K2.1, K3.1, K4.1, K5.1, K6.1, K7.1, K8.1, K9.1, K10.1, K11.1, K12.1, K13.1, K14.1, K15.1, K16.1, K17.1, K18.1, K19.1, K20.1, K21.1, K22.1, K23.1, K24.1, K25.1, K26.1, K27.1, K28.1, K29.1, K30.1, K31.1, K32.1, K33.1, K34.1, K35.1, K36.1, K37.1, K38.1, K39.1, K40.1, K41.1, K42.1, K43.1, K44.1, K45.1, K46.1, K47.1, K48.1, K49.1, K50.1, K51.1, K52.1, K53.1, K54.1, K55.1, K56.1, K57.1, K58.1, K59.1, K60.1, K61.1, K62.1, K63.1, K64.1, K65.1, K66.1, K67.1, K68.1, K69.1, K70.1, K71.1, K72.1, K73.1, K74.1, K75.1, K76.1, K77.1, K78.1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
unnamed: E1.2, E2.2, K1.2, K2.2, K3.2, K4.2, K5.2, K6.2, K7.2, K8.2, K9.2, K10.2, K11.2, K12.2, K13.2, K14.2, K15.2, K16.2, K17.2, K18.2, K19.2, K20.2, K21.2, K22.2, K23.2, K24.2, K25.2, K26.2, K27.2, K28.2, K29.2, K30.2, K31.2, K32.2, K33.2, K34.2, K35.2, K36.2, K37.2, K38.2, K39.2, K40.2, K41.2, K42.2, K43.2, K44.2, K45.2, K46.2, K47.2, K48.2, K49.2, K50.2, K51.2, K52.2, K53.2, K54.2, K55.2, K56.2, K57.2, K58.2, K59.2, K60.2, K61.2, K62.2, K63.2, K64.2, K65.2, K66.2, K67.2, K68.2, K69.2, K70.2, K71.2, K72.2, K73.2, K74.2, K75.2, K76.2, K77.2, K78.2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
unnamed: E1.3, E2.3, K1.3, K2.3, K3.3, K4.3, K5.3, K6.3, K7.3, K8.3, K9.3, K10.3, K11.3, K12.3, K13.3, K14.3, K15.3, K16.3, K17.3, K18.3, K19.3, K20.3, K21.3, K22.3, K23.3, K24.3, K25.3, K26.3, K27.3, K28.3, K29.3, K30.3, K31.3, K32.3, K33.3, K34.3, K35.3, K36.3, K37.3, K38.3, K39.3, K40.3, K41.3, K42.3, K43.3, K44.3, K45.3, K46.3, K47.3, K48.3, K49.3, K50.3, K51.3, K52.3, K53.3, K54.3, K55.3, K56.3, K57.3, K58.3, K59.3, K60.3, K61.3, K62.3, K63.3, K64.3, K65.3, K66.3, K67.3, K68.3, K69.3, K70.3, K71.3, K72.3, K73.3, K74.3, K75.3, K76.3, K77.3, K78.3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
unnamed: E1.4, E2.4, K1.4, K2.4, K3.4, K4.4, K5.4, K6.4, K7.4, K8.4, K9.4, K10.4, K11.4, K12.4, K13.4, K14.4, K15.4, K16.4, K17.4, K18.4, K19.4, K20.4, K21.4, K22.4, K23.4, K24.4, K25.4, K26.4, K27.4, K28.4, K29.4, K30.4, K31.4, K32.4, K33.4, K34.4, K35.4, K36.4, K37.4, K38.4, K39.4, K40.4, K41.4, K42.4, K43.4, K44.4, K45.4, K46.4, K47.4, K48.4, K49.4, K50.4, K51.4, K52.4, K53.4, K54.4, K55.4, K56.4, K57.4, K58.4, K59.4, K60.4, K61.4, K62.4, K63.4, K64.4, K65.4, K66.4, K67.4, K68.4, K69.4, K70.4, K71.4, K72.4, K73.4, K74.4, K75.4, K76.4, K77.4, K78.4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

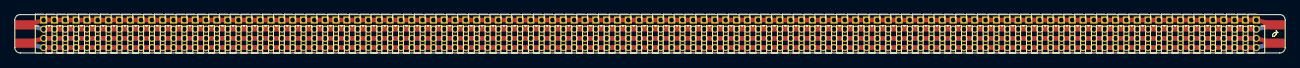
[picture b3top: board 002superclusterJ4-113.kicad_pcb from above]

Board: 2 copper layers, 176.0 x 5.3 mm, 115 parts (0 on the bottom side), 4 nets.

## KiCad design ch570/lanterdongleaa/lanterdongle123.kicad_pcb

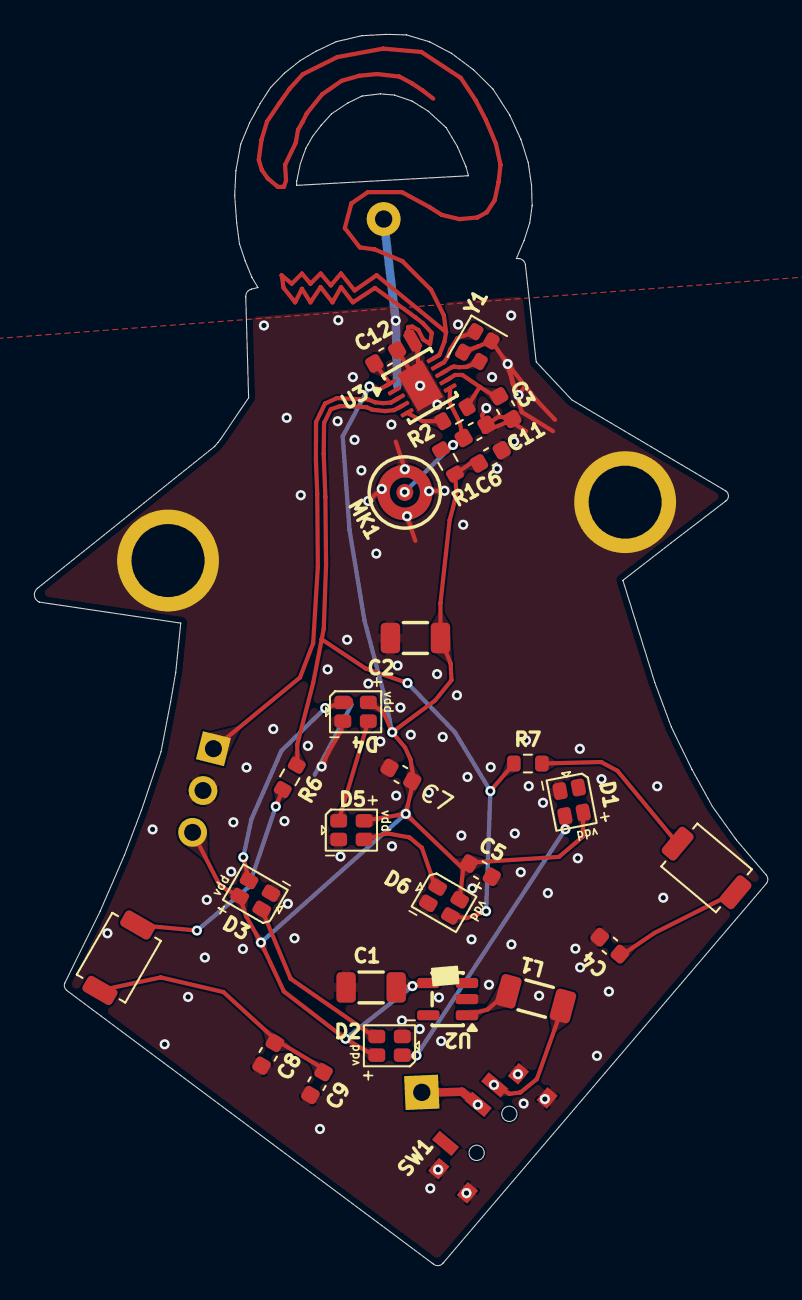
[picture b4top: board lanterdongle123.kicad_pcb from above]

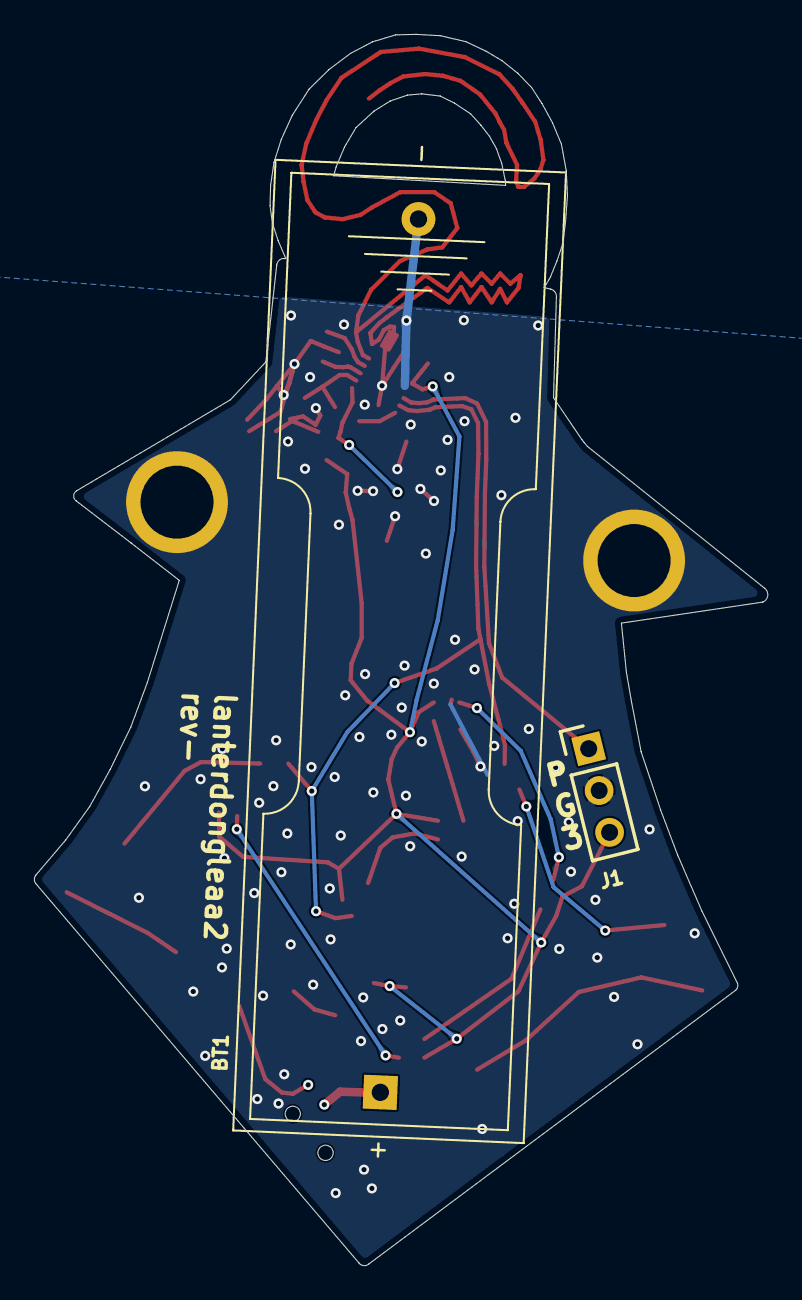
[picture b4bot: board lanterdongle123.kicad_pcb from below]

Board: 2 copper layers, 43.2 x 72.5 mm, 36 parts (2 on the bottom side), 22 nets.

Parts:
A1: toppart
A2: lanttopaa-outline
BT1: Battery_Cell; BatteryHolder_Keystone_2460_1xAA
C1, C2: 22uF; C_1206_3216Metric
C3, C4, C5, C6, C7, C8, C9, C11, C12: 10nF; C_0603_1608Metric
D1, D2, D3, D4, D5, D6: WS2812C_2020_XL_0807_RGB_LED
H1, H2: MountingHole_Pad; MountingHole_4.3mm_M4_DIN965_Pad
J1: PGM; PinHeader_1x03_P2.54mm_Vertical
L1: 4.7uH; L_1206_3216Metric_Pad1.22x1.90mm_HandSolder
MK1: Microphone; CUI_CMC-4013-SMT
NT1: NetTie_2; NetTie-2_SMD_Pad0.5mm
R1, R2, R6, R7: 4.7k; R_0603_1608Metric
SW1: PWR; SW_SPDT_PCM12
SW2, SW3: SW_SPST; SW_SPST_TS-1088-xR020
U2: TPS613221ADBV; SOT-23-5
U3: CH572Q; DFN-10-1EP_3x3mm_P0.5mm_EP1.7x2.5mm
Y1: 32M; Crystal_SMD_2016-4Pin_2.0x1.6mm

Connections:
+3.3V: C1.1, C2.1, C5.1, C6.1, C7.1, C12.1, D1.2 (V+), D2.2 (V+), D3.2 (V+), D4.2 (V+), D5.2 (V+), D6.2 (V+), J1.3, R1.1, U2.4 (VOUT), U3.1 (VDD33/VIO33)
GND: BT1.2 (-), C1.2, C2.2, C3.2, C4.2, C5.2, C6.2, C7.2, C8.2, C9.2, C11.1, C12.2, D1.3 (GND), D2.3 (GND), D3.3 (GND), D4.3 (GND), D5.3 (GND), D6.3 (GND), H1.1 (1_1), H2.1 (1_1), J1.2, MK1.1 (-), NT1.2, SW1.4, SW1.5, SW1.6, SW1.7, U2.2 (GND), U3.11 (GND), Y1.2, Y1.4
LED: D6.4 (DI), R6.1, R7.1, U3.4 (PA1/UDP/T2/R3/SDA/SWCLK)
unnamed: BT1.1 (+), SW1.2
unnamed: D1.4 (DI), D2.1 (DO)
unnamed: D2.4 (DI), D3.1 (DO)
unnamed: D3.4 (DI), D4.1 (DO)
unnamed: D4.4 (DI), D5.1 (DO)
unnamed: D5.4 (DI), D6.1 (DO)
unnamed: L1.1, SW1.3
unnamed: R7.2, SW2.1 (A)
unnamed: C4.1, SW2.2 (B)
unnamed: R6.2, SW3.1 (A)
unnamed: C8.1, C9.1, SW3.2 (B)
unnamed: L1.2, U2.1 (SW)
unnamed: NT1.1, U3.10 (ANT)
unnamed: U3.9 (XI), Y1.1
unnamed: U3.8 (XO), Y1.3
PA2: C11.2, MK1.2 (+), R1.2, U3.6 (PA2/R/T1/SDA2/TMR1/CMP_N)
PA3: C3.1, R2.2, U3.7 (PA3/T/R1/SCL2/CMP_P0/SCK_)
PWM: R2.1, U3.5 (PA7/T4/TMR/RST_/CAP_IN1/CMP_P1)
SWD: J1.1, U3.3 (PA0/UDM/R2/T3/SCL1/SWD)

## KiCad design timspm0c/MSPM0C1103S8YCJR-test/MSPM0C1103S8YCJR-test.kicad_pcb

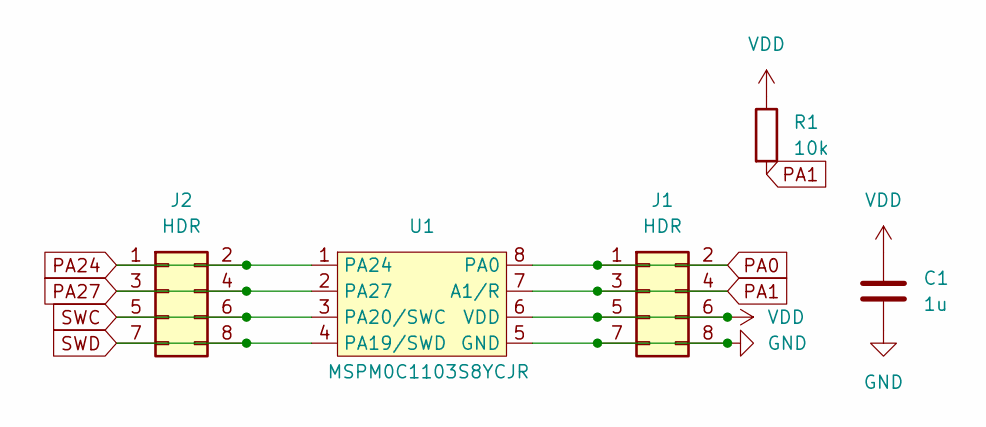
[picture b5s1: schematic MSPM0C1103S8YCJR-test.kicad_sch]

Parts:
C1: 1u; C_0402_1005Metric; LCSC C52923
J1, J2: HDR; PinHeader_2x04_P2.54mm_Vertical; LCSC C27985200
R1: 10k; R_0402_1005Metric; LCSC C25744
U1: MSPM0C1103S8YCJR; X2SON-8_1.4x1mm_P0.35mm-DBGA8-TIMSPM0C; LCSC C53449703

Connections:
GND: C1.2, J1.7, J1.8, U1.5 (GND)
PA0: J1.1, J1.2, U1.8 (PA0)
PA1: J1.3, J1.4, R1.2, U1.7 (A1/R)
PA24: J2.1, J2.2, U1.1 (PA24)
PA27: J2.3, J2.4, U1.2 (PA27)
SWC: J2.5, J2.6, U1.3 (PA20/SWC)
SWD: J2.7, J2.8, U1.4 (PA19/SWD)
VDD: C1.1, J1.5, J1.6, R1.1, U1.6 (VDD)

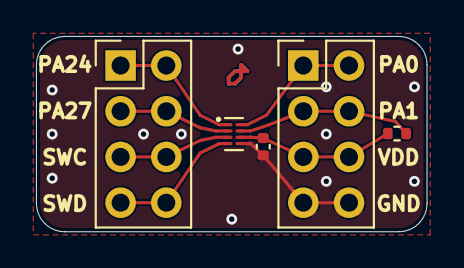
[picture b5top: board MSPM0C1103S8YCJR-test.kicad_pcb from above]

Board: 2 copper layers, 21.7 x 10.8 mm, 5 parts (0 on the bottom side), 8 nets.

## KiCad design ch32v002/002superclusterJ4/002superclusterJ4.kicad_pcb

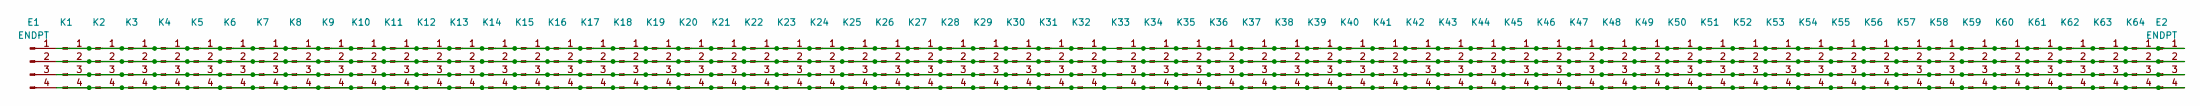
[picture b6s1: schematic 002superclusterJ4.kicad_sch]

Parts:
E1, E2: ENDPT; EDGE_02x02_2.54mm
K1, K2, K3, K4, K5, K6, K7, K8, K9, K10, K11, K12, K13, K14, K15, K16, K17, K18, K19, K20, K21, K22, K23, K24, K25, K26, K27, K28, K29, K30, K31, K32, K33, K34, K35, K36, K37, K38, K39, K40, K41, K42, K43, K44, K45, K46, K47, K48, K49, K50, K51, K52, K53, K54, K55, K56, K57, K58, K59, K60, K61, K62, K63, K64: PinHeader_1x04_P1.27mm_Vertical

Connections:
unnamed: E1.1, E2.1, K1.1, K2.1, K3.1, K4.1, K5.1, K6.1, K7.1, K8.1, K9.1, K10.1, K11.1, K12.1, K13.1, K14.1, K15.1, K16.1, K17.1, K18.1, K19.1, K20.1, K21.1, K22.1, K23.1, K24.1, K25.1, K26.1, K27.1, K28.1, K29.1, K30.1, K31.1, K32.1, K33.1, K34.1, K35.1, K36.1, K37.1, K38.1, K39.1, K40.1, K41.1, K42.1, K43.1, K44.1, K45.1, K46.1, K47.1, K48.1, K49.1, K50.1, K51.1, K52.1, K53.1, K54.1, K55.1, K56.1, K57.1, K58.1, K59.1, K60.1, K61.1, K62.1, K63.1, K64.1
unnamed: E1.2, E2.2, K1.2, K2.2, K3.2, K4.2, K5.2, K6.2, K7.2, K8.2, K9.2, K10.2, K11.2, K12.2, K13.2, K14.2, K15.2, K16.2, K17.2, K18.2, K19.2, K20.2, K21.2, K22.2, K23.2, K24.2, K25.2, K26.2, K27.2, K28.2, K29.2, K30.2, K31.2, K32.2, K33.2, K34.2, K35.2, K36.2, K37.2, K38.2, K39.2, K40.2, K41.2, K42.2, K43.2, K44.2, K45.2, K46.2, K47.2, K48.2, K49.2, K50.2, K51.2, K52.2, K53.2, K54.2, K55.2, K56.2, K57.2, K58.2, K59.2, K60.2, K61.2, K62.2, K63.2, K64.2
unnamed: E1.3, E2.3, K1.3, K2.3, K3.3, K4.3, K5.3, K6.3, K7.3, K8.3, K9.3, K10.3, K11.3, K12.3, K13.3, K14.3, K15.3, K16.3, K17.3, K18.3, K19.3, K20.3, K21.3, K22.3, K23.3, K24.3, K25.3, K26.3, K27.3, K28.3, K29.3, K30.3, K31.3, K32.3, K33.3, K34.3, K35.3, K36.3, K37.3, K38.3, K39.3, K40.3, K41.3, K42.3, K43.3, K44.3, K45.3, K46.3, K47.3, K48.3, K49.3, K50.3, K51.3, K52.3, K53.3, K54.3, K55.3, K56.3, K57.3, K58.3, K59.3, K60.3, K61.3, K62.3, K63.3, K64.3
unnamed: E1.4, E2.4, K1.4, K2.4, K3.4, K4.4, K5.4, K6.4, K7.4, K8.4, K9.4, K10.4, K11.4, K12.4, K13.4, K14.4, K15.4, K16.4, K17.4, K18.4, K19.4, K20.4, K21.4, K22.4, K23.4, K24.4, K25.4, K26.4, K27.4, K28.4, K29.4, K30.4, K31.4, K32.4, K33.4, K34.4, K35.4, K36.4, K37.4, K38.4, K39.4, K40.4, K41.4, K42.4, K43.4, K44.4, K45.4, K46.4, K47.4, K48.4, K49.4, K50.4, K51.4, K52.4, K53.4, K54.4, K55.4, K56.4, K57.4, K58.4, K59.4, K60.4, K61.4, K62.4, K63.4, K64.4

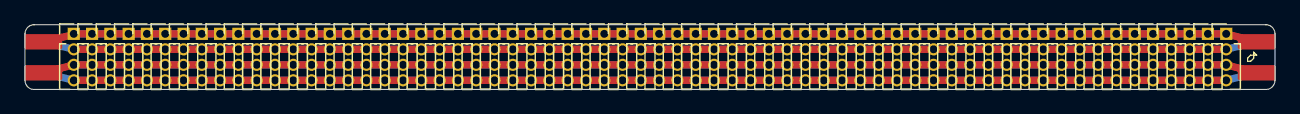
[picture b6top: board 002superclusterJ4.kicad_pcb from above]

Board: 2 copper layers, 102.5 x 5.3 mm, 66 parts (0 on the bottom side), 4 nets.

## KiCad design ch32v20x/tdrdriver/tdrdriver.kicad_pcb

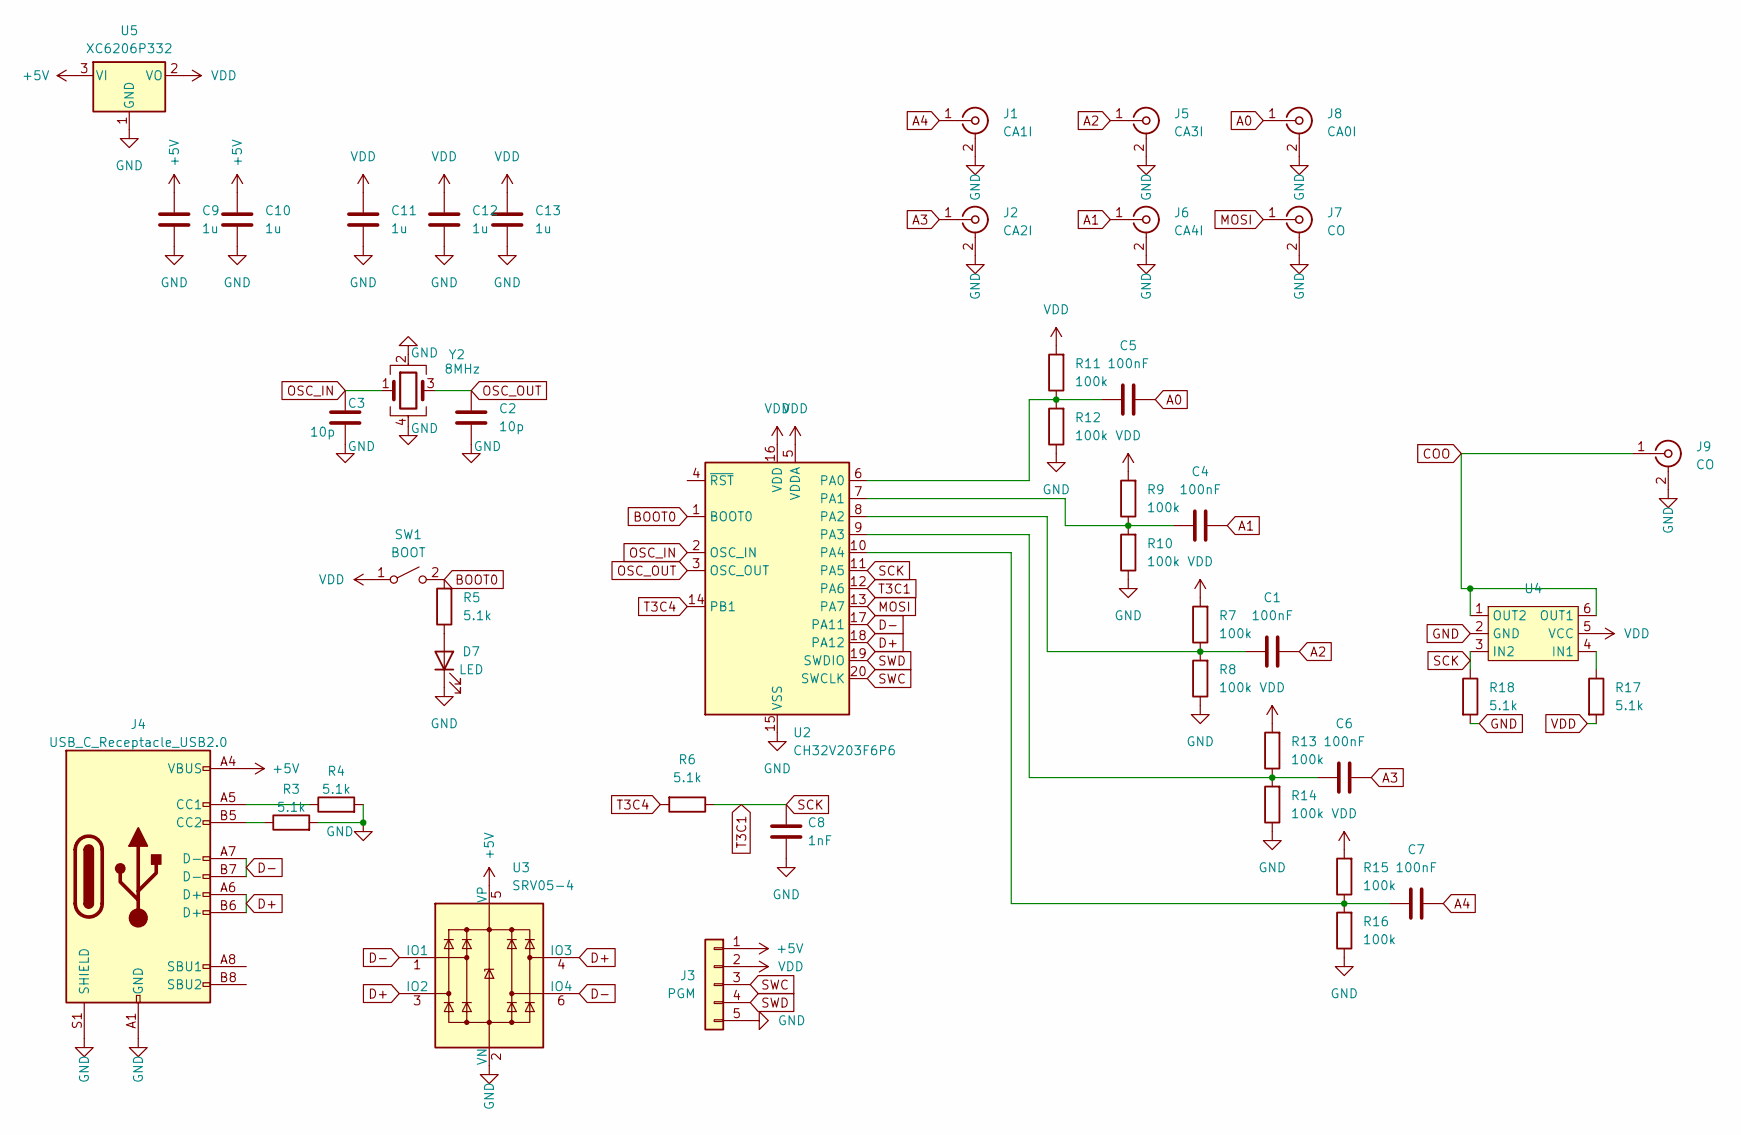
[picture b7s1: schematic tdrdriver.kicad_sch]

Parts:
C1, C4, C5, C6, C7: 100nF; C_0402_1005Metric; LCSC C1525
C2, C3: 10p; C_0402_1005Metric; LCSC C32949
C8: 1nF; C_0402_1005Metric; LCSC C1523
C9, C10, C11, C12, C13: 1u; C_0402_1005Metric; LCSC C52923
D7: LED; LED_0603_1608Metric; LCSC C2290
J1: CA1I; SMA_Samtec_SMA-J-P-H-ST-EM1_EdgeMount
J2: CA2I; SMA_Samtec_SMA-J-P-H-ST-EM1_EdgeMount
J3: PGM; PinHeader_1x05_P2.54mm_Vertical; LCSC C492404
J4: USB_C_Receptacle_USB2.0; USB_C_Receptacle_HRO_TYPE-C-31-M-12; LCSC C2765186
J5: CA3I; SMA_Samtec_SMA-J-P-H-ST-EM1_EdgeMount
J6: CA4I; SMA_Samtec_SMA-J-P-H-ST-EM1_EdgeMount
J7, J9: CO; SMA_Samtec_SMA-J-P-H-ST-EM1_EdgeMount
J8: CA0I; SMA_Samtec_SMA-J-P-H-ST-EM1_EdgeMount
R3, R4, R5, R6, R17, R18: 5.1k; R_0402_1005Metric; LCSC C25905
R7, R8, R9, R10, R11, R12, R13, R14, R15, R16: 100k; R_0402_1005Metric; LCSC C25741
SW1: BOOT; TS-1187A-B-A-B-TACTILE; LCSC C318884
U2: CH32V203F6P6; TSSOP-20_4.4x6.5mm_P0.65mm; LCSC C3040880
U3: SRV05-4; SOT-23-6; LCSC C2836319
U4: SOT-23-6; LCSC C16197225
U5: XC6206P332; SOT-23; LCSC C5446
Y2: 8MHz; Crystal_SMD_3225-4Pin_3.2x2.5mm; LCSC C400090

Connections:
+5V: C9.1, C10.1, J3.1, J4.A4 (VBUS), J4.A9 (VBUS), J4.B4 (VBUS), J4.B9 (VBUS), U3.5 (VP), U5.3 (VI)
A0: C5.2, J8.1 (In)
A1: C4.2, J6.1 (In)
A2: C1.2, J5.1 (In)
A3: C6.2, J2.1 (In)
A4: C7.2, J1.1 (In)
BOOT0: R5.2, SW1.2 (B), U2.1 (BOOT0)
COO: J9.1 (In), U4.1 (OUT2), U4.6 (OUT1)
D+: J4.A6 (D+), J4.B6 (D+), U2.18 (PA12), U3.3 (IO2), U3.4 (IO3)
D-: J4.A7 (D-), J4.B7 (D-), U2.17 (PA11), U3.1 (IO1), U3.6 (IO4)
GND: C2.2, C3.2, C8.1, C9.2, C10.2, C11.2, C12.2, C13.2, D7.1 (K), J1.2 (Ext), J2.2 (Ext), J3.5, J4.A1 (GND), J4.A12 (GND), J4.B1 (GND), J4.B12 (GND), J4.S1 (SHIELD), J5.2 (Ext), J6.2 (Ext), J7.2 (Ext), J8.2 (Ext), J9.2 (Ext), R3.2, R4.2, R8.1, R10.1, R12.1, R14.1, R16.1, R18.2, U2.15 (VSS), U3.2 (VN), U4.2 (GND), U5.1 (GND), Y2.2, Y2.4
MOSI: J7.1 (In), U2.13 (PA7)
unnamed: D7.2 (A), R5.1
unnamed: J4.A5 (CC1), R4.1
unnamed: J4.B5 (CC2), R3.1
unnamed: C5.1, R11.1, R12.2, U2.6 (PA0)
unnamed: C4.1, R9.1, R10.2, U2.7 (PA1)
unnamed: C1.1, R7.1, R8.2, U2.8 (PA2)
unnamed: C6.1, R13.1, R14.2, U2.9 (PA3)
unnamed: C7.1, R15.1, R16.2, U2.10 (PA4)
unnamed: R17.1, U4.4 (IN1)
OSC_IN: C3.1, U2.2 (OSC_IN), Y2.1
OSC_OUT: C2.1, U2.3 (OSC_OUT), Y2.3
SCK: C8.2, R6.1, R18.1, U2.11 (PA5), U2.12 (PA6), U4.3 (IN2)
SWC: J3.3, U2.20 (SWCLK)
SWD: J3.4, U2.19 (SWDIO)
T3C4: R6.2, U2.14 (PB1)
VDD: C11.1, C12.1, C13.1, J3.2, R7.2, R9.2, R11.2, R13.2, R15.2, R17.2, SW1.1 (A), U2.5 (VDDA), U2.16 (VDD), U4.5 (VCC), U5.2 (VO)
